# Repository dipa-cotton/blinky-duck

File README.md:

# blinky-duck
## Why I made this
An LED board shaped like a duck for adorableness :3

I wanted to create this project to learn more about the fundamentals of PCB design, because I felt like i jumped straight into things like hackpads without appreciating the fundamentals and actually understanding what everything does.

I learned about various different components, like a potentiometer, from this project, and I believe my skills have improved with this mini ducky <3

## Pictures of my beautiful ducky
3D Render:

Routed PCB:

Schematic:

## BOM:

PCB	-	$5.00	-	JLCPCB	
Polarized Capacitor	PCB -	$3.00	-	AliExpress	
Potentiometer/Variable Resistor	PCB -	$2.00	-	AliExpress	
ICM7555	PCB -	$3.00	-	AliExpress

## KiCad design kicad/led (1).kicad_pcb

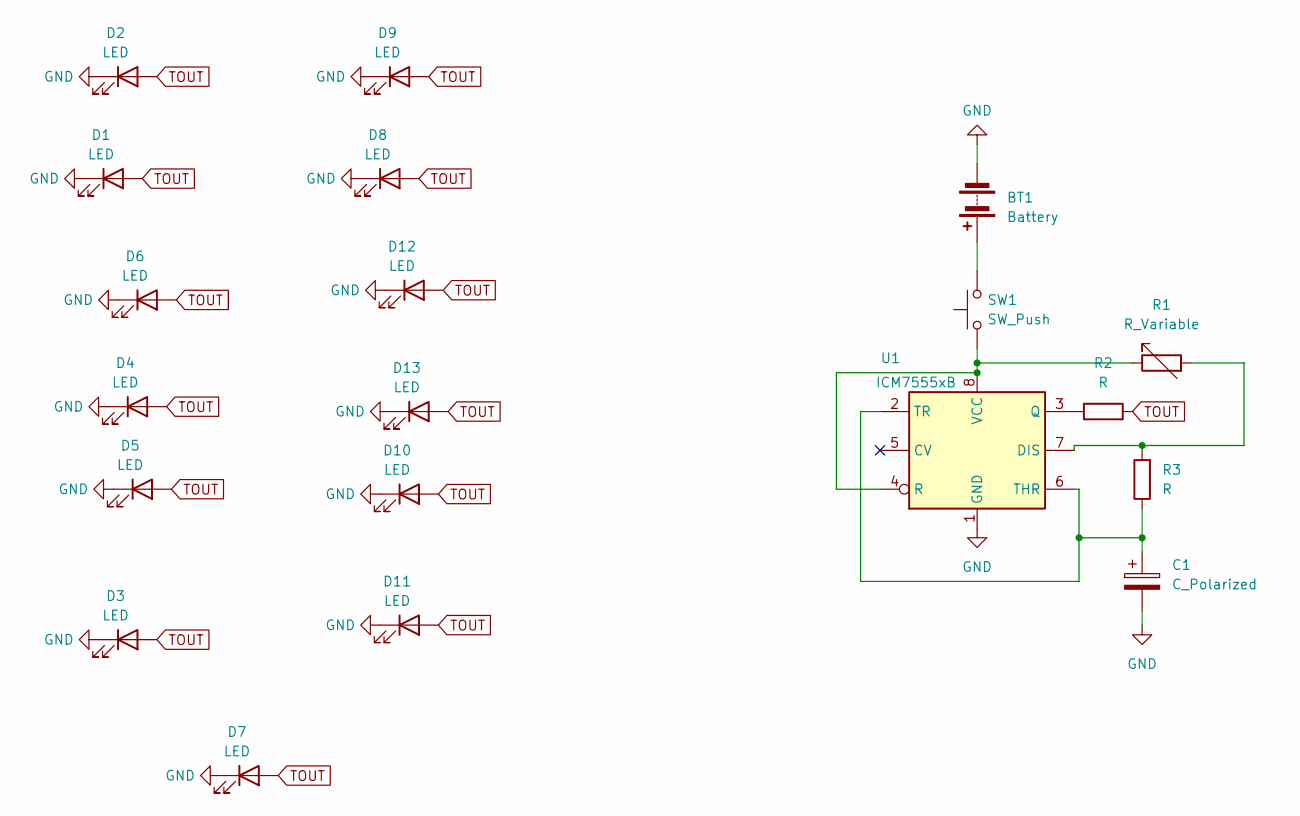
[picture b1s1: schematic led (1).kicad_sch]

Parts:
BT1: Battery; SolderWire-2.5sqmm_1x02_P7.2mm_D2.4mm_OD3.6mm
C1: C_Polarized; CP_Radial_D5.0mm_P2.50mm
D1, D2, D3, D4, D5, D6, D7, D8, D9, D10, D11, D12, D13: LED; LED_D5.0mm
R1: R_Variable; Potentiometer_Bourns_3386P_Vertical
R2, R3: R; R_Axial_DIN0207_L6.3mm_D2.5mm_P7.62mm_Horizontal
SW1: SW_Push; SW_PUSH_6mm
U1: ICM7555xB; SOIC-8_3.9x4.9mm_P1.27mm

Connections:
GND: BT1.2 (-), C1.2, D1.1 (K), D2.1 (K), D3.1 (K), D4.1 (K), D5.1 (K), D6.1 (K), D7.1 (K), D8.1 (K), D9.1 (K), D10.1 (K), D11.1 (K), D12.1 (K), D13.1 (K), U1.1 (GND)
unnamed: BT1.1 (+), SW1.2
unnamed: R1.2, R3.2, U1.7 (DIS)
unnamed: R2.2, U1.3 (Q)
unnamed: R1.1, SW1.1, U1.4 (R), U1.8 (VCC)
unnamed: C1.1, R3.1, U1.2 (TR), U1.6 (THR)
TOUT: D1.2 (A), D2.2 (A), D3.2 (A), D4.2 (A), D5.2 (A), D6.2 (A), D7.2 (A), D8.2 (A), D9.2 (A), D10.2 (A), D11.2 (A), D12.2 (A), D13.2 (A), R2.1

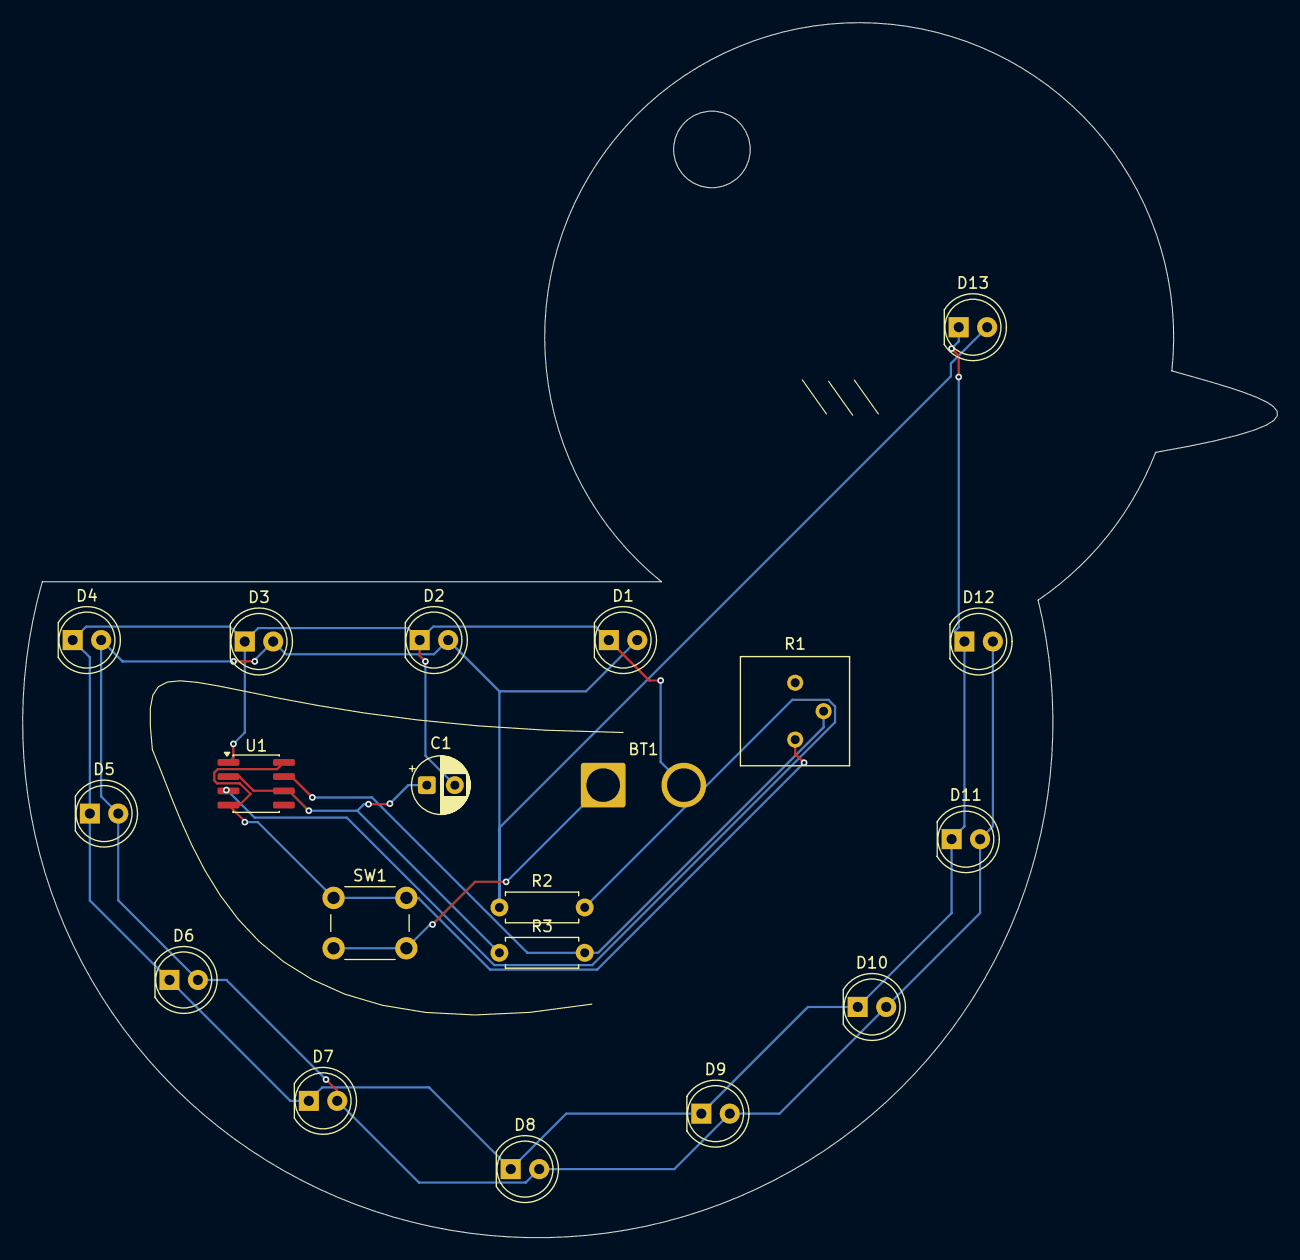
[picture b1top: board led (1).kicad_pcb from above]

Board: 2 copper layers, 112.0 x 108.5 mm, 20 parts (0 on the bottom side), 7 nets.

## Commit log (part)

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2026-04-12 Create l
2026-06-23 Expand README with project motivation and BOM
    Added a section explaining the motivation behind the project and included pictures of the ducky along with a Bill of Materials (BOM) listing components and their costs.
